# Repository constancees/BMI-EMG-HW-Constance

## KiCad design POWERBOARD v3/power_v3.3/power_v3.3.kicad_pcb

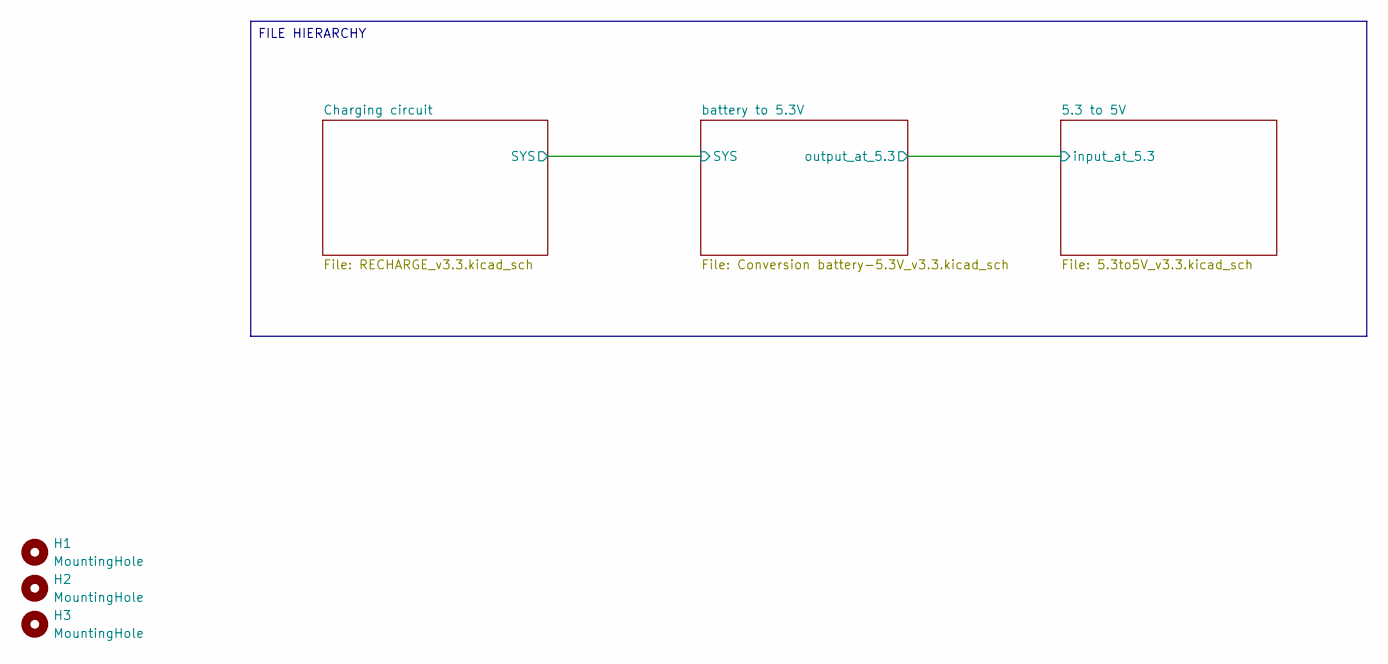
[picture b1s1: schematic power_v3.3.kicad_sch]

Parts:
H1, H2, H3: MountingHole; MountingHole_2.2mm_M2_DIN965_Pad

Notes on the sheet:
FILE HIERARCHY

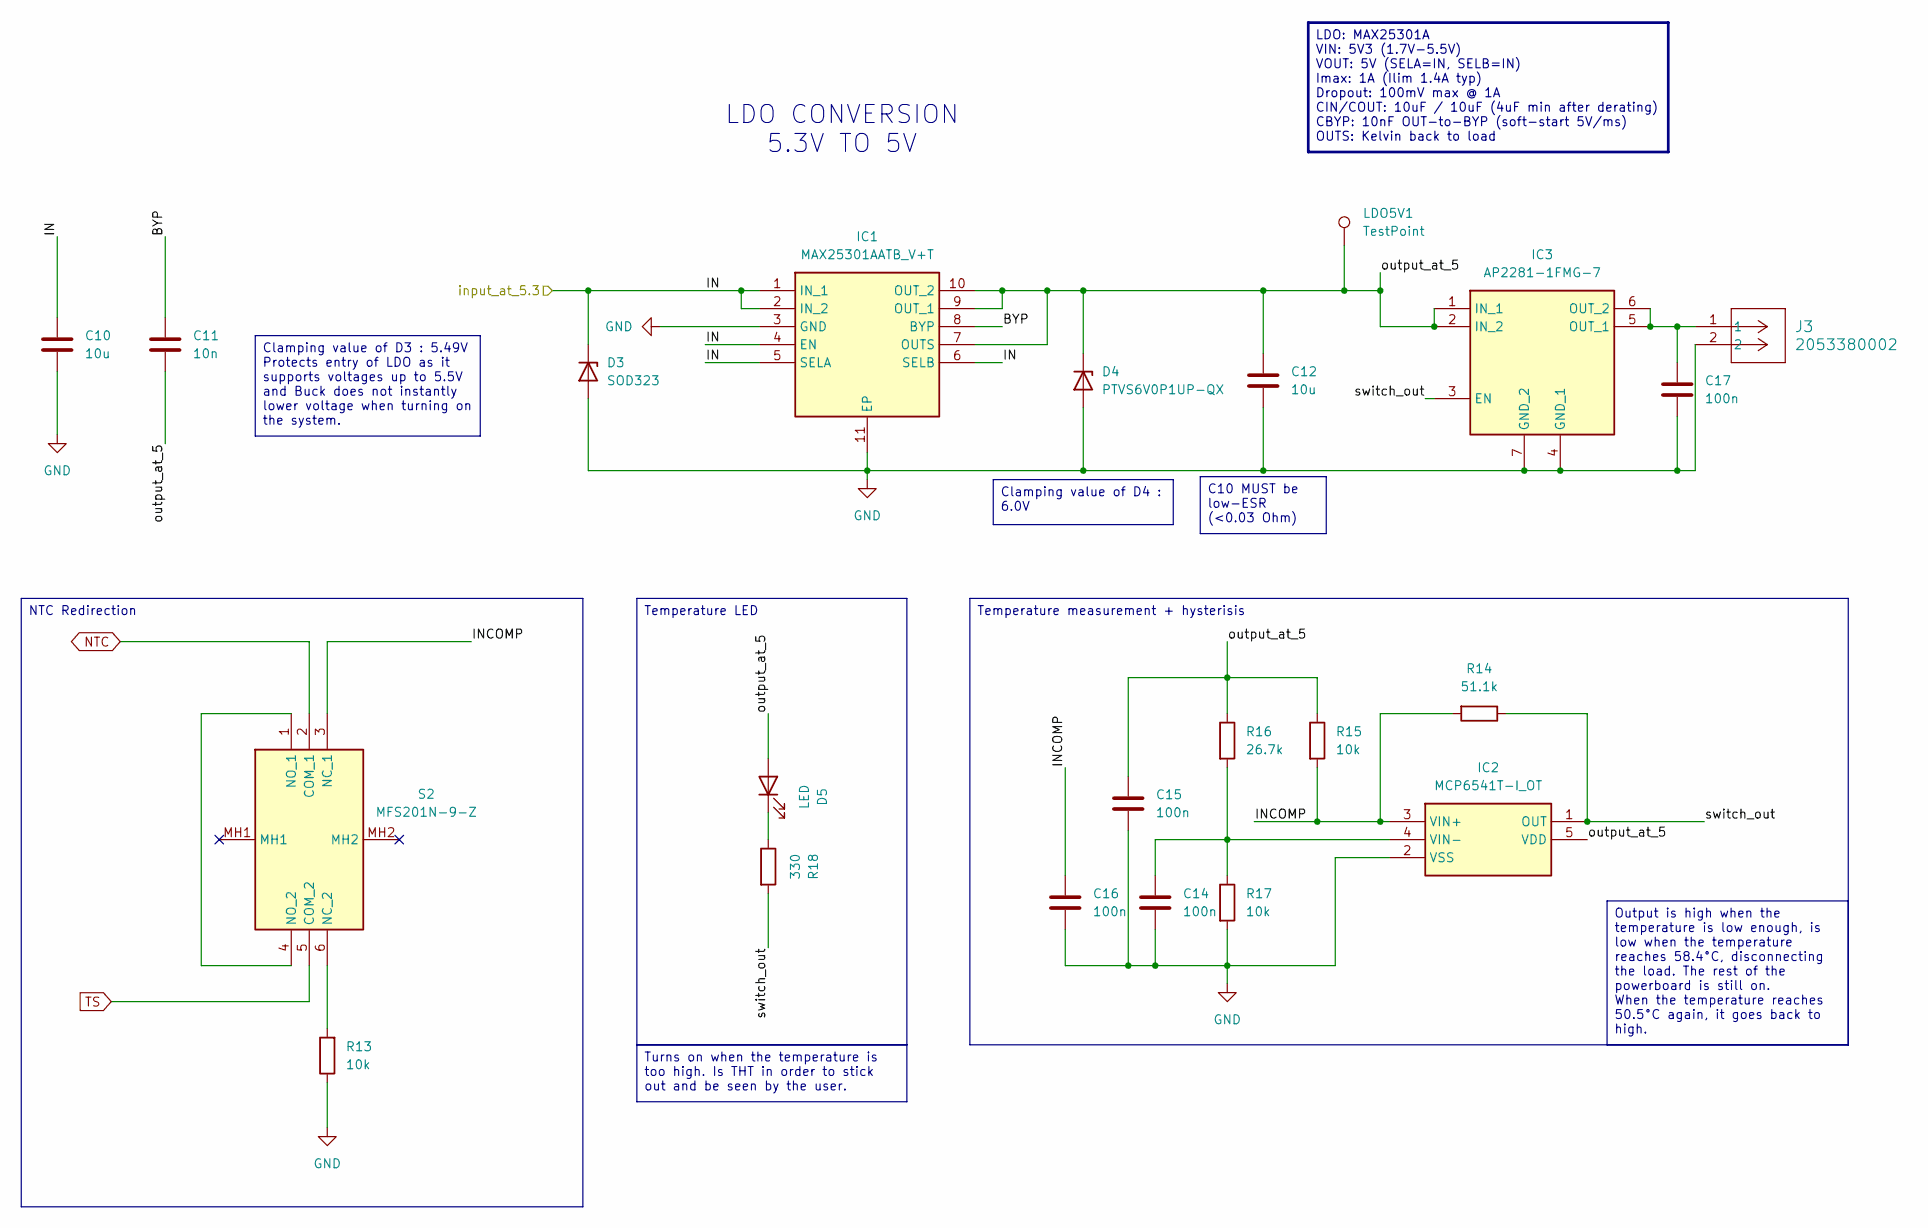
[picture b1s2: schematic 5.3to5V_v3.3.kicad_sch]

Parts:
C10, C12: 10u; C_0805_2012Metric
C11: 10n; C_0402_1005Metric
C14, C15, C16, C17: 100n; C_0402_1005Metric
D3: SOD323; SOT-23
D4: PTVS6V0P1UP-QX; D_SOD-128
D5: LED; LED_D5.0mm
IC1: MAX25301AATB_V+T; SON50P300X300X80-11N; Mouser Part Number 700-MAX25301AATB/V+T
IC2: MCP6541T-I_OT; SOT95P270X145-5N; Mouser Part Number 579-MCP6541T-I/OT
IC3: AP2281-1FMG-7; SON50P201X181X60-7N; Mouser Part Number 621-AP2281-1FMG-7
J3: 2053380002; CONN_2053380000-SD_02_MOL
LDO5V1: TestPoint; TestPoint_Keystone_5000-5004_Miniature
R13, R15, R17: 10k; R_0603_1608Metric
R14: 51.1k; R_0603_1608Metric
R16: 26.7k; R_0603_1608Metric
R18: 330; R_0603_1608Metric
S2: MFS201N-9-Z; MFS201N9Z; Mouser Part Number 229-MFS201N-9-Z

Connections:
/5.3 to 5V/BYP: C11.1, IC1.8 (BYP)
/5.3 to 5V/IN: C10.1, D3.1 (K), IC1.1 (IN_1), IC1.2 (IN_2), IC1.4 (EN), IC1.5 (SELA), IC1.6 (SELB); also elsewhere on the board
/5.3 to 5V/INCOMP: C16.1, IC2.3 (VIN+), R14.2, R15.2, S2.3 (NC_1)
/5.3 to 5V/output_at_5: C11.2, C12.1, C15.1, D4.1 (K), D5.2 (A), IC1.7 (OUTS), IC1.9 (OUT_1), IC1.10 (OUT_2), IC2.5 (VDD), IC3.1 (IN_1), IC3.2 (IN_2), LDO5V1.1 (1_1), R15.1, R16.1
/5.3 to 5V/switch_out: IC2.1 (OUT), IC3.3 (EN), R14.1, R18.2
GND: C10.2, C12.2, C14.2, C15.2, C16.2, C17.2, D3.2 (A), D4.2 (A), IC1.3 (GND), IC1.11 (EP), IC2.2 (VSS), IC3.4 (GND_1), IC3.7 (GND_2), J3.2, R13.1, R17.2; also elsewhere on the board
NTC: S2.2 (COM_1), S2.5 (COM_2); also elsewhere on the board
unnamed: D5.1 (K), R18.1
unnamed: C14.1, IC2.4 (VIN-), R16.2, R17.1
unnamed: C17.1, IC3.5 (OUT_1), IC3.6 (OUT_2), J3.1
unnamed: R13.2, S2.6 (NC_2)
unnamed: S2.1 (NO_1), S2.4 (NO_2)

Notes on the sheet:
LDO CONVERSION 5.3V TO 5V
LDO: MAX25301A VIN: 5V3 (1.7V-5.5V) VOUT: 5V (SELA=IN, SELB=IN) Imax: 1A (Ilim 1.4A typ) Dropout: 100mV max @ 1A CIN/COUT: 10uF / 10uF (4uF min after derating) CBYP: 10nF OUT-to-BYP (soft-start 5V/ms) OUTS: Kelvin back to load
Clamping value of D4 : 6.0V
Temperature LED
Clamping value of D3 : 5.49V Protects entry of LDO as it supports voltages up to 5.5V and Buck does not instantly lower voltage when turning on the system.
C10 MUST be low-ESR (<0.03 Ohm)
Temperature measurement + hysterisis
Output is high when the temperature is low enough, is low when the temperature reaches 58.4°C, disconnecting the load. The rest of the powerboard is still on. When the temperature reaches 50.5°C again, it goes back to high.
Turns on when the temperature is too high. Is THT in order to stick out and be seen by the user.
NTC Redirection

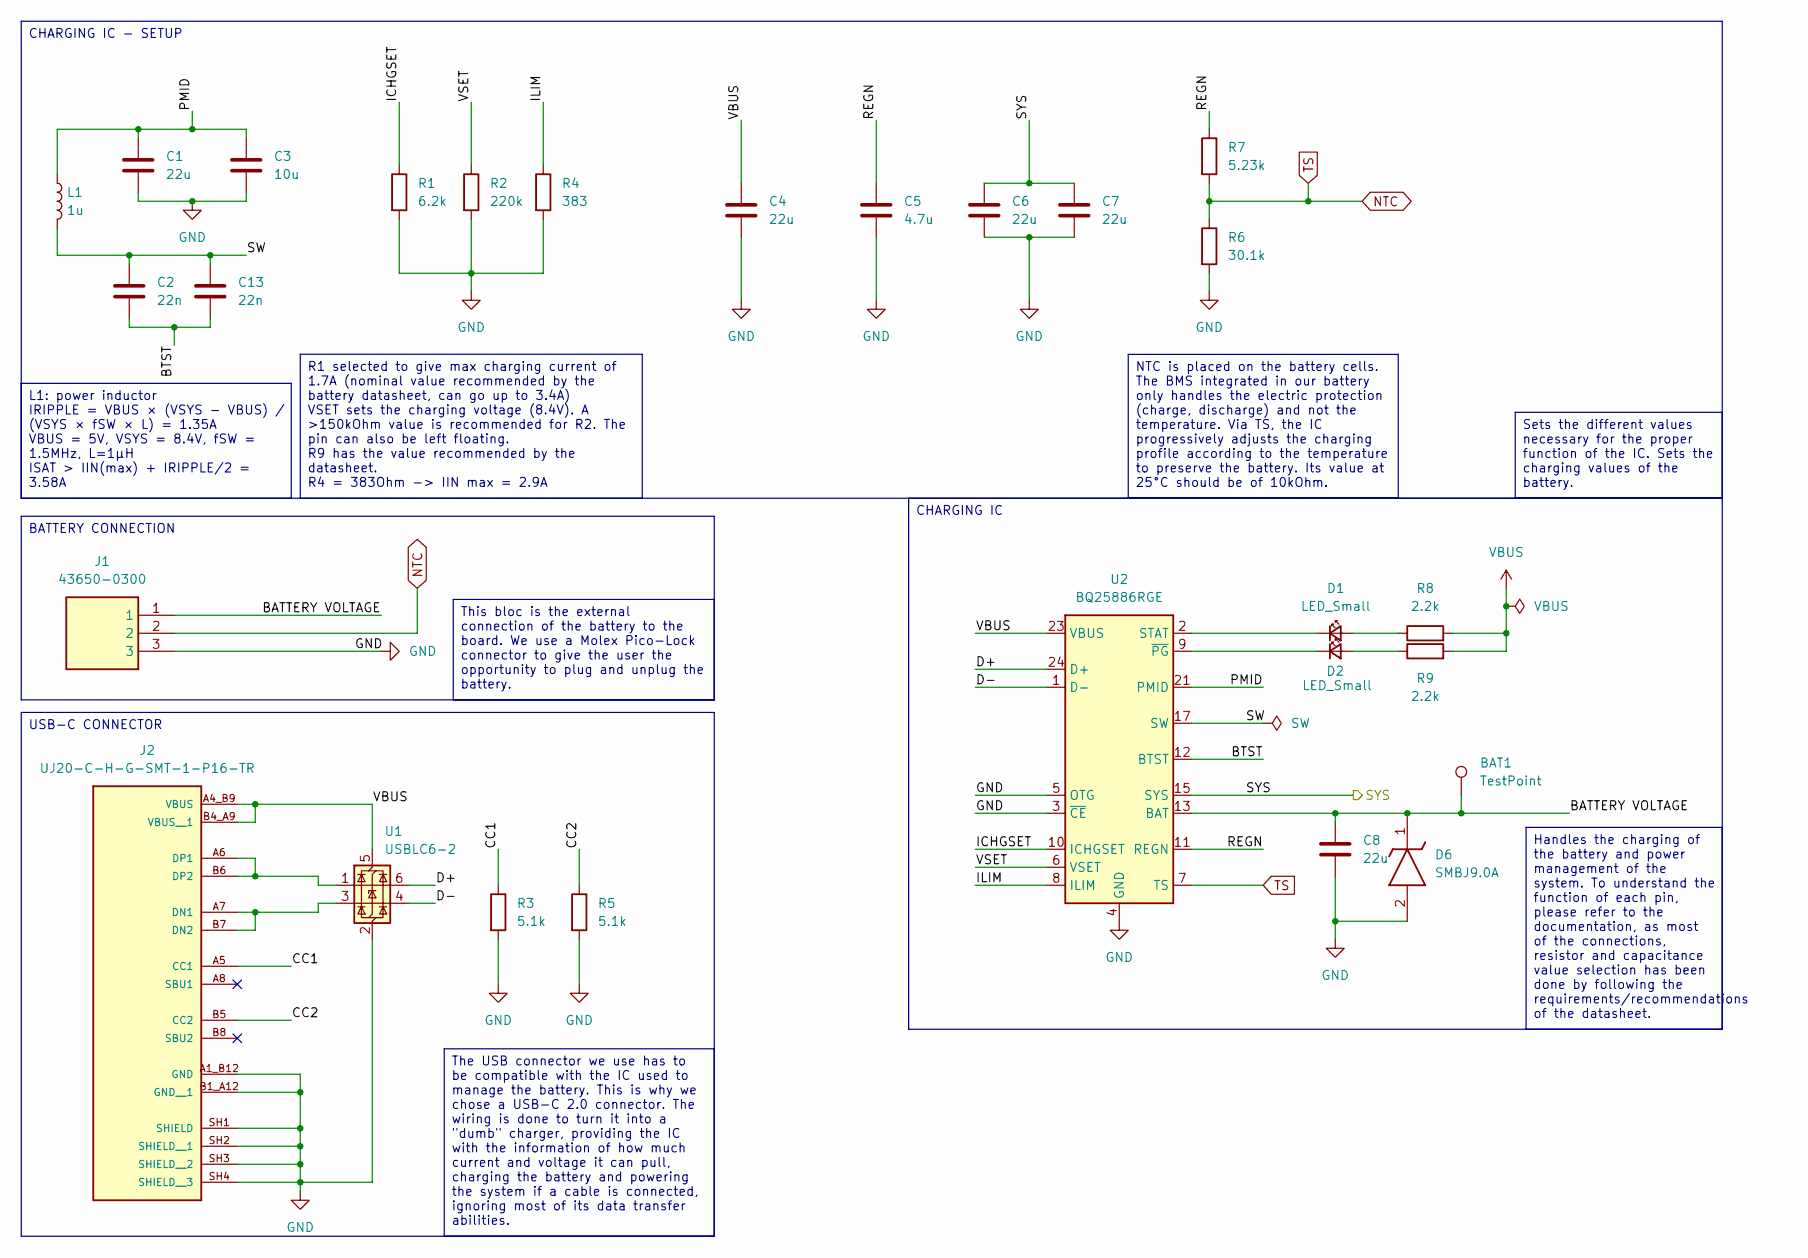
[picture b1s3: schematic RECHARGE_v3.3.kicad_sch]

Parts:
BAT1: TestPoint; TestPoint_Keystone_5000-5004_Miniature
C1, C4, C6, C7, C8: 22u; C_1206_3216Metric
C2, C13: 22n; C_0201_0603Metric
C3: 10u; C_0805_2012Metric
C5: 4.7u; C_0805_2012Metric
D1, D2: LED_Small; LED_0603_1608Metric
D6: SMBJ9.0A; DIOM5436X261N; Manufacturer_Part_Number SMBJ9.0A
J1: 43650-0300; 436500300; Mouser Part Number 538-43650-0300
J2: UJ20-C-H-G-SMT-1-P16-TR; SAMESKY_UJ20-C-H-G-SMT-1-P16-TR; PARTREV 1.0
L1: 1u; INDC3030X200N
R1: 6.2k; R_0603_1608Metric
R2: 220k; R_0603_1608Metric
R3, R5: 5.1k; R_0603_1608Metric
R4: 383; R_0603_1608Metric
R6: 30.1k; R_0603_1608Metric
R7: 5.23k; R_0603_1608Metric
R8, R9: 2.2k; R_0603_1608Metric
U1: USBLC6-2; SOT-23-6
U2: BQ25886RGE; Texas_RGE0024H_VQFN-24-1EP_4x4mm_P0.5mm_EP2.7x2.7mm

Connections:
/Charging circuit/BATTERY VOLTAGE: BAT1.1 (1_1), C8.1, D6.1 (K), J1.1, U2.13 (BAT), U2.14 (BAT)
/Charging circuit/BTST: C2.2, C13.2, U2.12 (BTST)
/Charging circuit/CC1: J2.A5 (CC1), R3.1
/Charging circuit/CC2: J2.B5 (CC2), R5.1
/Charging circuit/D+: U1.6 (I/O1), U2.24 (D+)
/Charging circuit/D-: U1.4 (I/O2), U2.1 (D-)
/Charging circuit/ICHGSET: R1.1, U2.10 (ICHGSET)
/Charging circuit/ILIM: R4.1, U2.8 (ILIM)
/Charging circuit/PMID: C1.1, C3.1, L1.1, U2.21 (PMID), U2.22 (PMID)
/Charging circuit/REGN: C5.1, R7.1, U2.11 (REGN)
/Charging circuit/SW: C2.1, C13.1, L1.2, U2.17 (SW), U2.18 (SW)
/Charging circuit/SYS: C6.1, C7.1, U2.15 (SYS), U2.16 (SYS); also elsewhere on the board
/Charging circuit/VSET: R2.1, U2.6 (VSET)
GND: C1.2, C3.2, C4.2, C5.2, C6.2, C7.2, C8.2, D6.2 (A), J1.3, J2.A1_B12 (GND), J2.B1_A12 (GND__1), J2.SH1 (SHIELD), J2.SH2 (SHIELD__1), J2.SH3 (SHIELD__2), J2.SH4 (SHIELD__3), R1.2, R2.2, R3.2, R4.2, R5.2, R6.2, U1.2 (GND), U2.3 (~CE), U2.4 (GND), U2.5 (OTG), U2.19 (GND), U2.20 (GND), U2.25 (GND); also elsewhere on the board
NTC: J1.2, R6.1, R7.2, U2.7 (TS); also elsewhere on the board
unnamed: D1.2 (A), R8.1
unnamed: D1.1 (K), U2.2 (STAT)
unnamed: D2.2 (A), R9.1
unnamed: D2.1 (K), U2.9 (~PG)
unnamed: J2.A7 (DN1), J2.B7 (DN2), U1.3 (I/O2)
unnamed: J2.A6 (DP1), J2.B6 (DP2), U1.1 (I/O1)
VBUS: C4.1, J2.A4_B9 (VBUS), J2.B4_A9 (VBUS__1), R8.2, R9.2, U1.5 (VBUS), U2.23 (VBUS)

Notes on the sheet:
R1 selected to give max charging current of 1.7A (nominal value recommended by the battery datasheet, can go up to 3.4A) VSET sets the charging voltage (8.4V). A >150kOhm value is recommended for R2. The pin can also be left floating. R9 has the value recommended by the datasheet. R4 = 383Ohm -> II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
This bloc is the external connection of the battery to the board. We use a Molex Pico-Lock connector to give the user the opportunity to plug and unplug the battery.
BATTERY CONNECTION
Sets the different values necessary for the proper function of the IC. Sets the charging values of the battery.
CHARGING IC - SETUP
Handles the charging of the battery and power management of the system. To understand the function of each pin, please refer to the documentation, as most of the connections, resistor and capacitance value selection has been done by following the requirements/recommendations of the datasheet.
CHARGING IC
NTC is placed on the battery cells. The BMS integrated in our battery only handles the electric protection (charge, discharge) and not the temperature. Via TS, the IC progressively adjusts the charging profile according to the temperature to preserve the battery. Its value at 25°C should be of 10kO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
USB-C CONNECTOR
The USB connector we use has to be compatible with the IC used to manage the battery. This is why we chose a USB-C 2.0 connector. The wiring is done to turn it into a "dumb" charger, providing the IC with the information of how much current and voltage it can pull, charging the battery and powering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
L1: power inductor IRIPPLE = VBUS × (VSYS − VBUS) / (VSYS × fSW × L) = 1.35A VBUS = 5V, VSYS = 8.4V, fSW = 1.5MHz, L=1µH ISAT > IIN(max) + IRIPPLE/2 = 3.58A

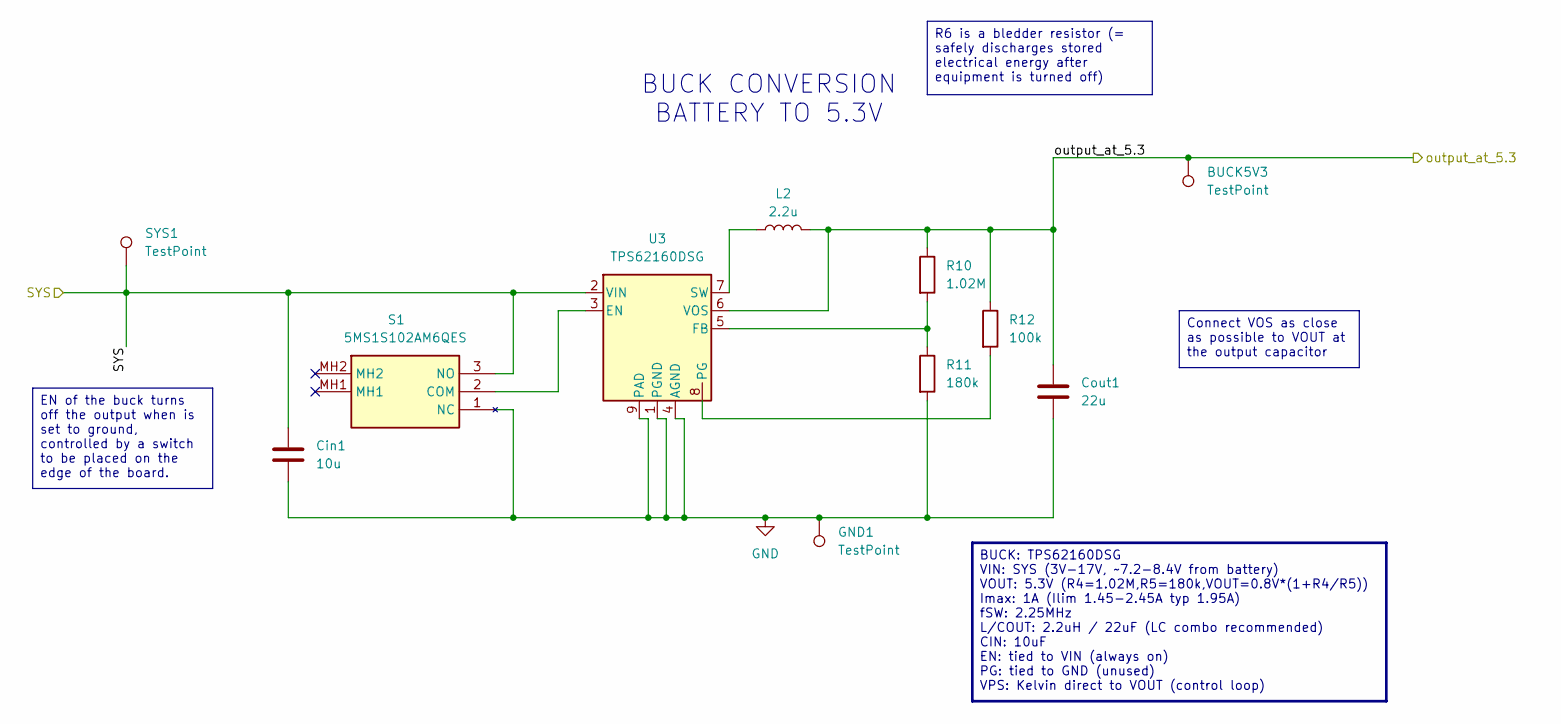
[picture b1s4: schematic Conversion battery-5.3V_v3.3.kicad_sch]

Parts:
BUCK5V3: TestPoint; TestPoint_Keystone_5000-5004_Miniature
Cin1: 10u; C_0805_2012Metric
Cout1: 22u; C_1206_3216Metric
GND1: TestPoint; TestPoint_Keystone_5000-5004_Miniature
L2: 2.2u; 78438336022
R10: 1.02M; R_0603_1608Metric
R11: 180k; R_0603_1608Metric
R12: 100k; R_0603_1608Metric
S1: 5MS1S102AM6QES; Mouser Part Number 118-5MS1S102AM6QES
SYS1: TestPoint; TestPoint_Keystone_5000-5004_Miniature
U3: TPS62160DSG; SON50P200X200X80-9N

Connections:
/5.3 to 5V/IN: BUCK5V3.1 (1_1), Cout1.1, L2.2, R10.1, R12.1, U3.6 (VOS); also elsewhere on the board
/Charging circuit/SYS: Cin1.1, S1.3 (NO), SYS1.1 (1_1), U3.2 (VIN); also elsewhere on the board
GND: Cin1.2, Cout1.2, GND1.1 (1_1), R11.2, S1.1 (NC), U3.1 (PGND), U3.4 (AGND), U3.9 (PAD); also elsewhere on the board
unnamed: S1.2 (COM), U3.3 (EN)
unnamed: R10.2, R11.1, U3.5 (FB)
unnamed: R12.2, U3.8 (PG)
unnamed: L2.1, U3.7 (SW)

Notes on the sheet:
BUCK CONVERSION BATTERY TO 5.3V
BUCK: TPS62160DSG VIN: SYS (3V-17V, ~7.2-8.4V from battery) VOUT: 5.3V (R4=1.02M,R5=180k,VOUT=0.8V*(1+R4/R5)) Imax: 1A (Ilim 1.45-2.45A typ 1.95A) fSW: 2.25MHz L/COUT: 2.2uH / 22uF (LC combo recommended) CIN: 10uF EN: tied to VIN (always on) PG: tied to GND (unused) VPS: Kelvin direct to VOUT (cont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
EN of the buck turns off the output when is set to ground, controlled by a switch to be placed on the edge of the board.
Connect VOS as close as possible to VOUT at the output capacitor
R6 is a bledder resistor (= safely discharges stored electrical energy after equipment is turned off)

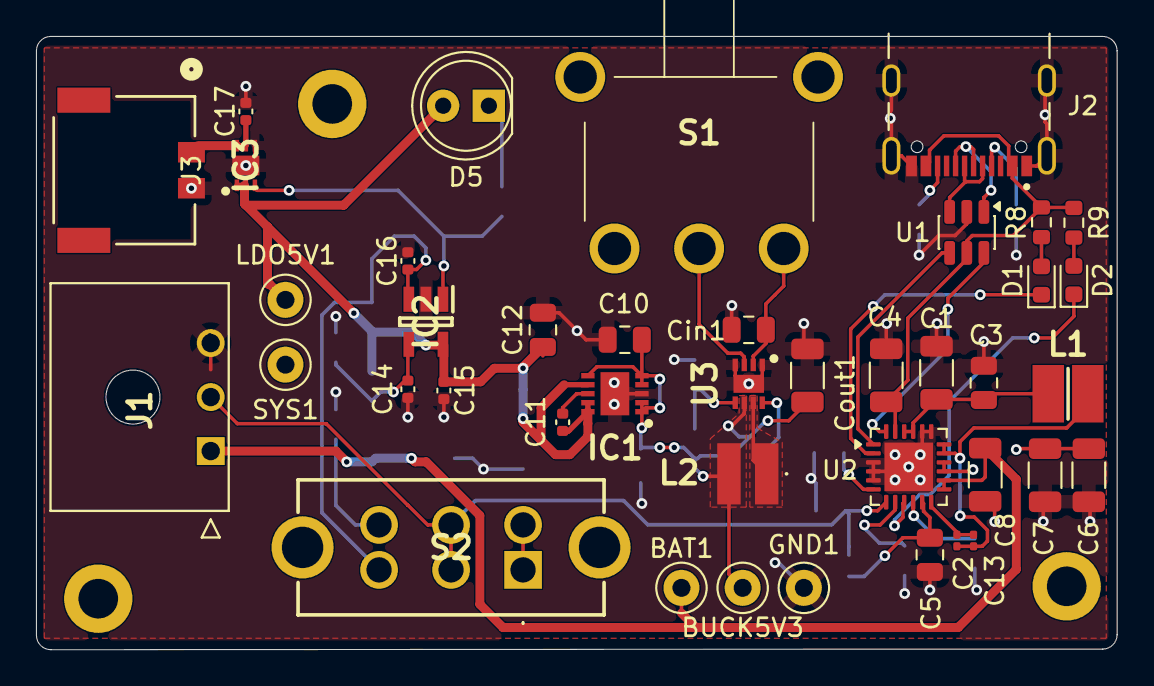
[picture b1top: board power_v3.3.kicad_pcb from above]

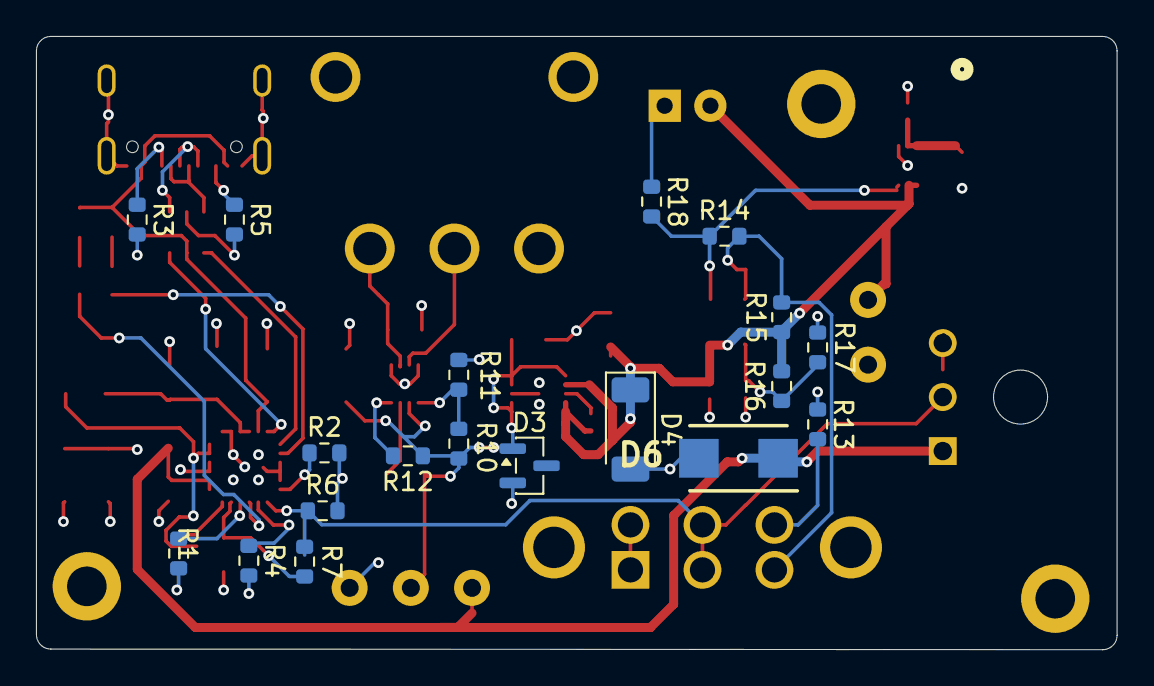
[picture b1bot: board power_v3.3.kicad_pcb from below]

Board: 4 copper layers, 60.0 x 34.1 mm, 63 parts (19 on the bottom side), 36 nets.

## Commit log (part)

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2026-05-24 Bracelets 2025-2026 ajoutés
